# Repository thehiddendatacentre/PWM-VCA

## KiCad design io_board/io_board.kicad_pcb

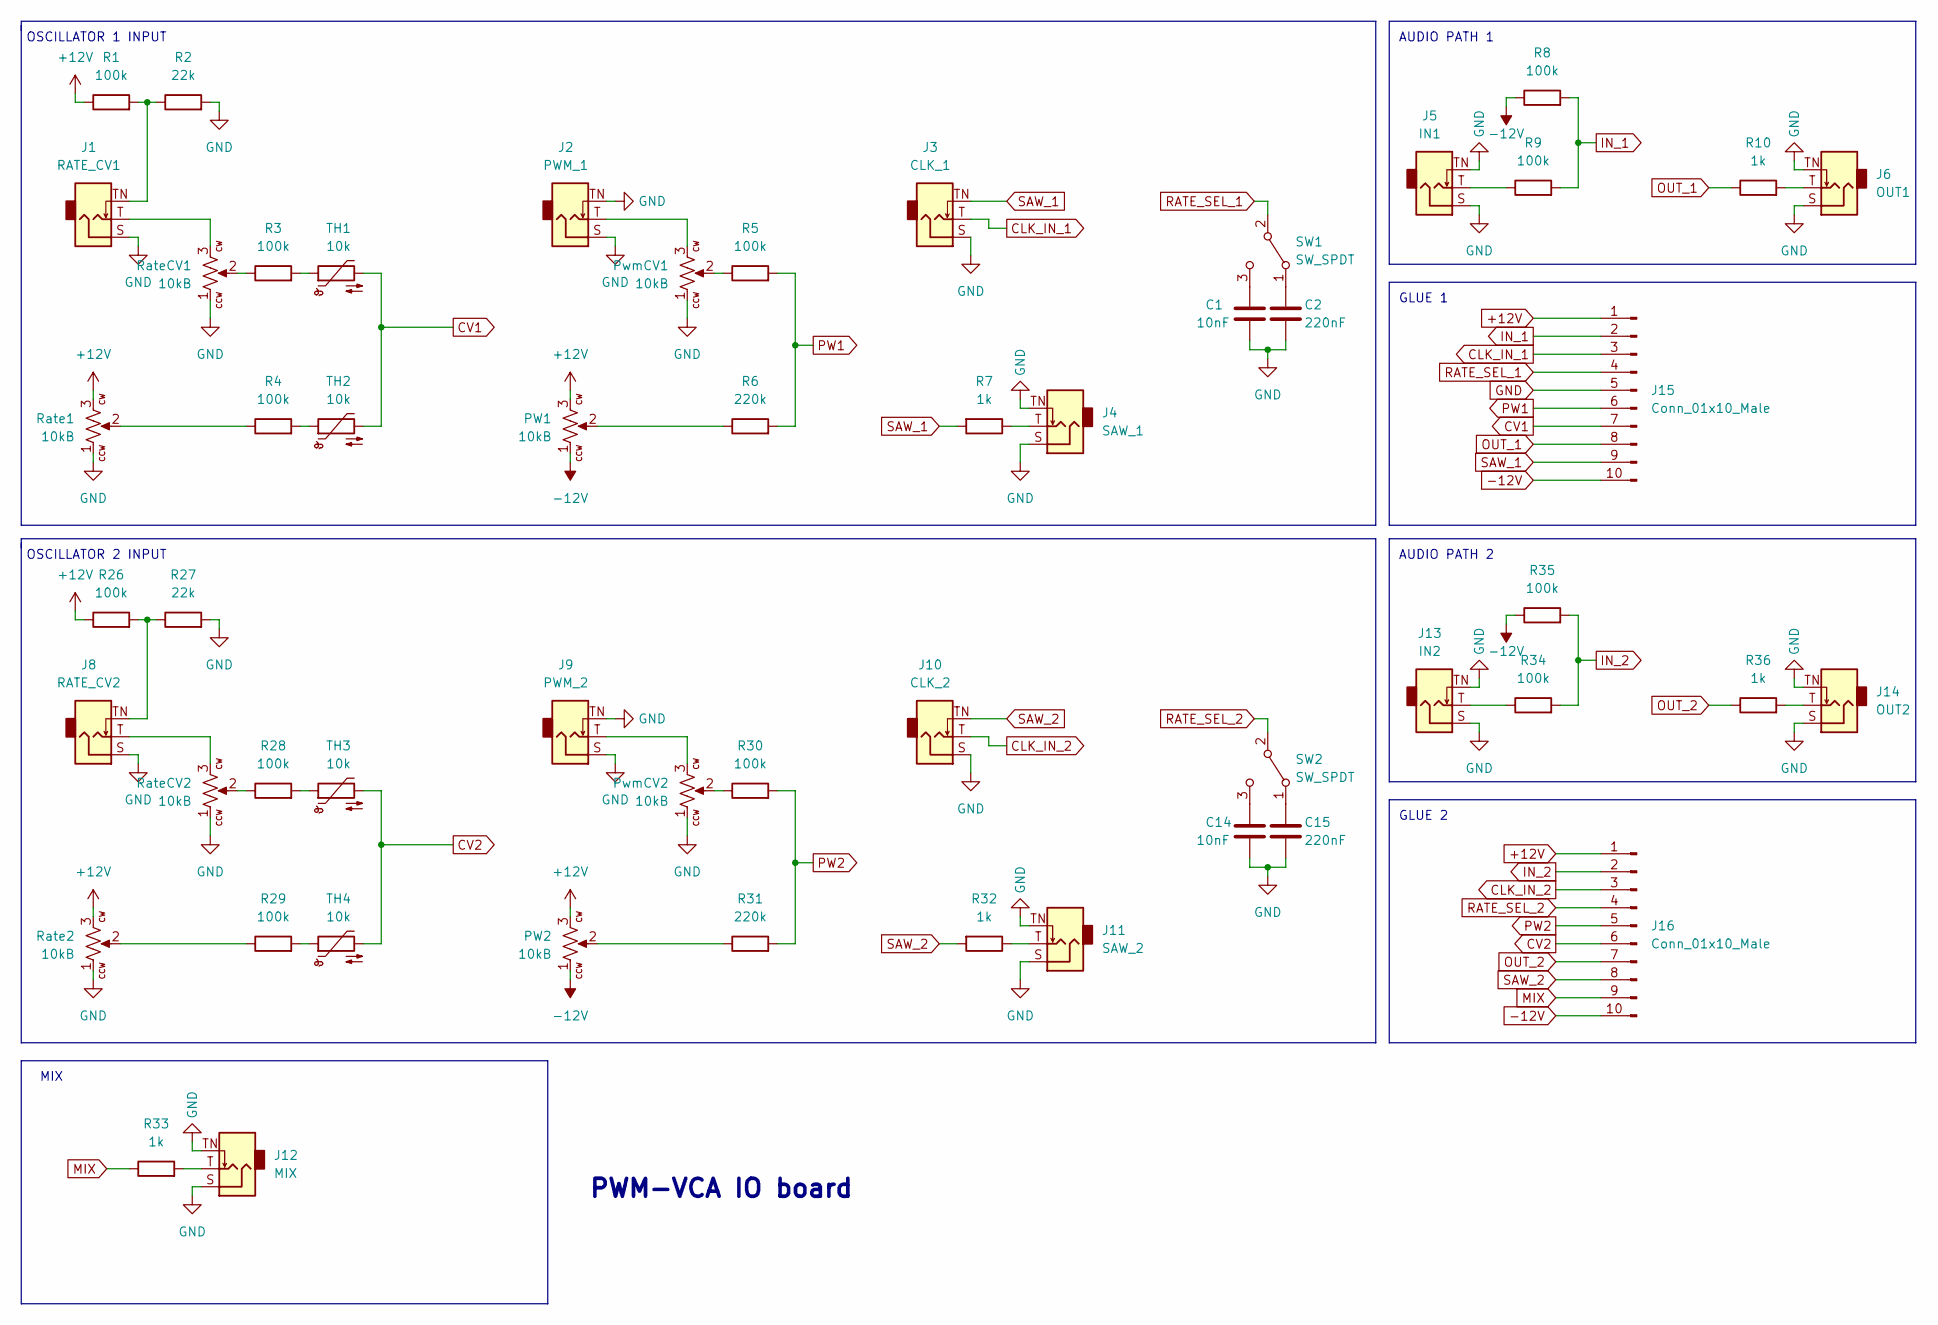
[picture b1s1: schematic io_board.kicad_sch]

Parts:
C1, C14: 10nF; C_Disc_D5.0mm_W2.5mm_P2.50mm
C2, C15: 220nF; C_Disc_D5.0mm_W2.5mm_P2.50mm
J1: RATE_CV1; AudioJack_WQP518MA; MPN WQP-WQP518MA
J2: PWM_1; AudioJack_WQP518MA; MPN WQP-WQP518MA
J3: CLK_1; AudioJack_WQP518MA; MPN WQP-WQP518MA
J4: SAW_1; AudioJack_WQP518MA; MPN WQP-WQP518MA
J5: IN1; AudioJack_WQP518MA; MPN WQP-WQP518MA
J6: OUT1; AudioJack_WQP518MA; MPN WQP-WQP518MA
J8: RATE_CV2; AudioJack_WQP518MA; MPN WQP-WQP518MA
J9: PWM_2; AudioJack_WQP518MA; MPN WQP-WQP518MA
J10: CLK_2; AudioJack_WQP518MA; MPN WQP-WQP518MA
J11: SAW_2; AudioJack_WQP518MA; MPN WQP-WQP518MA
J12: MIX; AudioJack_WQP518MA; MPN WQP-WQP518MA
J13: IN2; AudioJack_WQP518MA; MPN WQP-WQP518MA
J14: OUT2; AudioJack_WQP518MA; MPN WQP-WQP518MA
J15, J16: Conn_01x10_Male
PW1, PW2: 10kB; Potentiometer_Alpha_R0904N; MPN R0904N-???? L-25KQ/LWS
PwmCV1, PwmCV2: 10kB; Potentiometer_Alpha_R0904N; MPN R0904N-???? L-25KQ/LWS
R1, R3, R4, R5, R8, R9, R26, R28, R29, R30, R34, R35: 100k; R_Axial_DIN0204_L3.6mm_D1.6mm_P7.62mm_Horizontal
R2, R27: 22k; R_Axial_DIN0204_L3.6mm_D1.6mm_P7.62mm_Horizontal
R6, R31: 220k; R_Axial_DIN0204_L3.6mm_D1.6mm_P7.62mm_Horizontal
R7, R10, R32, R33, R36: 1k; R_Axial_DIN0204_L3.6mm_D1.6mm_P7.62mm_Horizontal
Rate1, Rate2: 10kB; Potentiometer_Alpha_R0904N; MPN R0904N-???? L-25KQ/LWS
RateCV1, RateCV2: 10kB; Potentiometer_Alpha_R0904N; MPN R0904N-???? L-25KQ/LWS
SW1, SW2: SW_SPDT; Miniature_Switch_SPDT_2.54MM
TH1, TH2, TH3, TH4: 10k; R_Axial_DIN0204_L3.6mm_D1.6mm_P2.54mm_Vertical

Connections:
+12V: J15.1, J16.1, PW1.3, PW2.3, R1.1, R26.1, Rate1.3, Rate2.3
-12V: J15.10, J16.10, PW1.1, PW2.1, R8.1, R35.1
CLK_IN_1: J3.T (Tip), J15.3
CLK_IN_2: J10.T (Tip), J16.3
CV1: J15.7, TH1.2, TH2.2
CV2: J16.6, TH3.2, TH4.2
GND: C1.2, C2.2, C14.2, C15.2, J1.S (Sleeve), J2.S (Sleeve), J2.TN (Tip_normalize), J3.S (Sleeve), J4.S (Sleeve), J4.TN (Tip_normalize), J5.S (Sleeve), J5.TN (Tip_normalize), J6.S (Sleeve), J6.TN (Tip_normalize), J8.S (Sleeve), J9.S (Sleeve), J9.TN (Tip_normalize), J10.S (Sleeve), J11.S (Sleeve), J11.TN (Tip_normalize), J12.S (Sleeve), J12.TN (Tip_normalize), J13.S (Sleeve), J13.TN (Tip_normalize), J14.S (Sleeve), J14.TN (Tip_normalize), J15.5, PwmCV1.1, PwmCV2.1, R2.2, R27.2, Rate1.1, Rate2.1, RateCV1.1, RateCV2.1
IN_1: J15.2, R8.2, R9.2
IN_2: J16.2, R34.2, R35.2
MIX: J16.9, R33.1
unnamed: C1.1, SW1.3 (C)
unnamed: C2.1, SW1.1 (A)
unnamed: C14.1, SW2.3 (C)
unnamed: C15.1, SW2.1 (A)
unnamed: J1.T (Tip), RateCV1.3
unnamed: J1.TN (Tip_normalize), R1.2, R2.1
unnamed: J2.T (Tip), PwmCV1.3
unnamed: J4.T (Tip), R7.1
unnamed: J5.T (Tip), R9.1
unnamed: J6.T (Tip), R10.2
unnamed: J8.T (Tip), RateCV2.3
unnamed: J8.TN (Tip_normalize), R26.2, R27.1
unnamed: J9.T (Tip), PwmCV2.3
unnamed: J11.T (Tip), R32.1
unnamed: J12.T (Tip), R33.2
unnamed: J13.T (Tip), R34.1
unnamed: J14.T (Tip), R36.2
unnamed: PW1.2, R6.1
unnamed: PW2.2, R31.1
unnamed: PwmCV1.2, R5.1
unnamed: PwmCV2.2, R30.1
unnamed: R3.1, RateCV1.2
unnamed: R3.2, TH1.1
unnamed: R4.1, Rate1.2
unnamed: R4.2, TH2.1
unnamed: R28.1, RateCV2.2
unnamed: R28.2, TH3.1
unnamed: R29.1, Rate2.2
unnamed: R29.2, TH4.1
OUT_1: J15.8, R10.1
OUT_2: J16.7, R36.1
PW1: J15.6, R5.2, R6.2
PW2: J16.5, R30.2, R31.2
RATE_SEL_1: J15.4, SW1.2 (B)
RATE_SEL_2: J16.4, SW2.2 (B)
SAW_1: J3.TN (Tip_normalize), J15.9, R7.2
SAW_2: J10.TN (Tip_normalize), J16.8, R32.2

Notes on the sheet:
AUDIO PATH 2
GLUE 1
MIX
OSCILLATOR 2 INPUT
OSCILLATOR 1 INPUT
GLUE 2
PWM-VCA IO board
AUDIO PATH 1

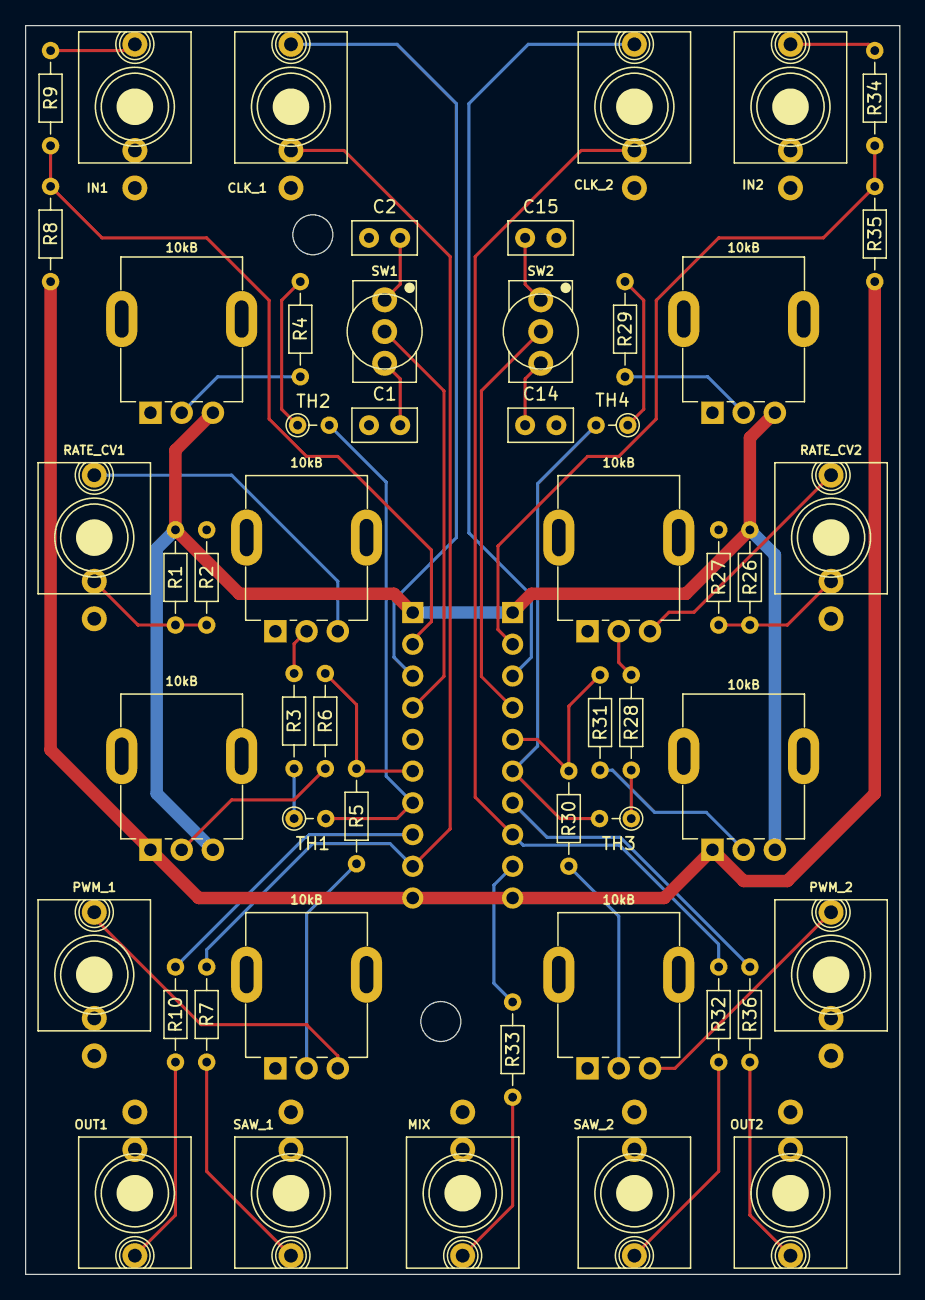
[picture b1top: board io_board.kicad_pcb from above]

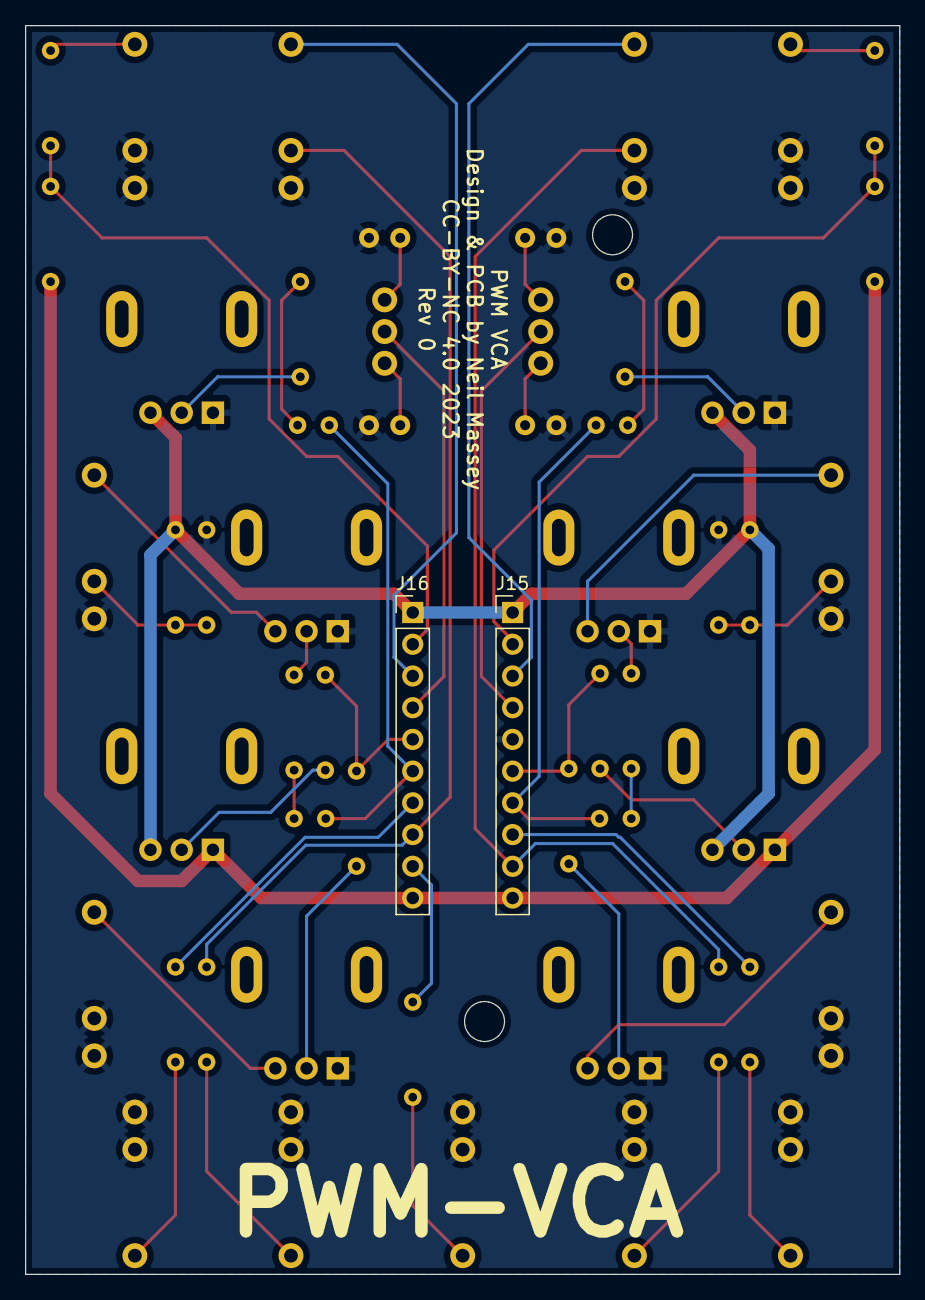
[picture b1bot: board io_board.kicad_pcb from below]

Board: 2 copper layers, 70.0 x 100.0 mm, 54 parts (2 on the bottom side), 47 nets.

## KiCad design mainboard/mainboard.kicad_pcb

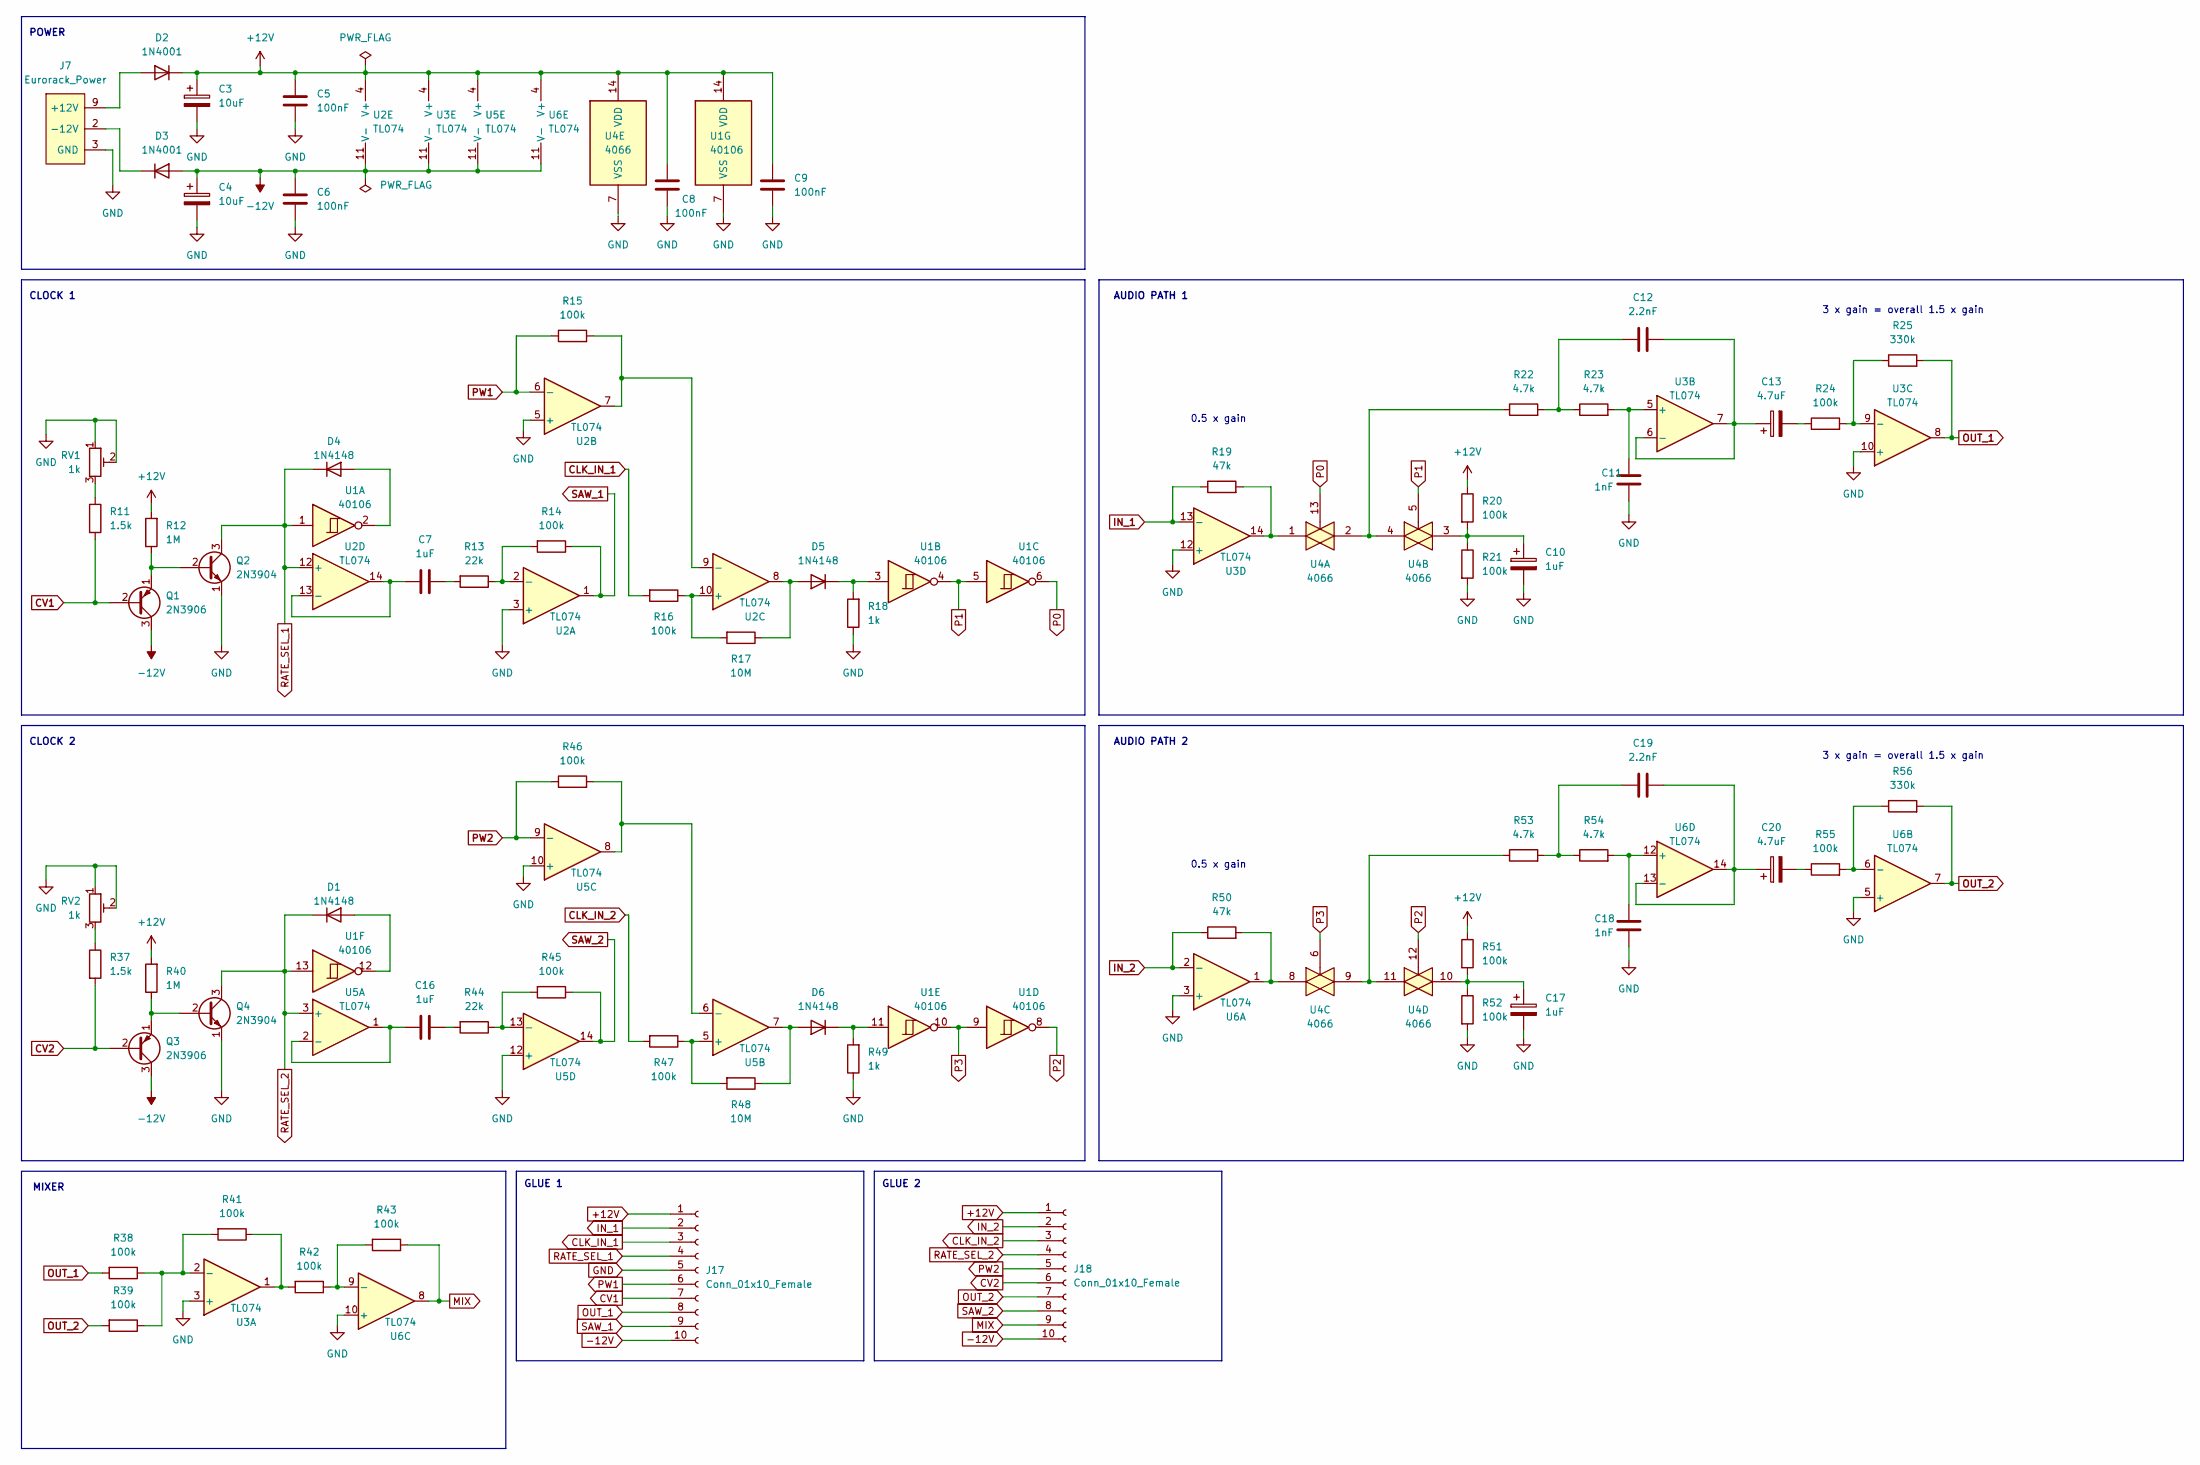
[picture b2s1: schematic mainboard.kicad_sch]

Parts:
C3, C4: 10uF; CP_Radial_D5.0mm_P2.00mm
C5, C6: 100nF; C_Disc_D5.0mm_W2.5mm_P2.50mm
C7, C16: 1uF; C_Disc_D5.0mm_W2.5mm_P2.50mm
C8, C9: 100nF; C_Disc_D7.0mm_W2.5mm_P5.00mm
C10, C17: 1uF; CP_Radial_D5.0mm_P2.00mm
C11, C18: 1nF; C_Disc_D7.5mm_W2.5mm_P5.00mm
C12, C19: 2.2nF; C_Disc_D7.5mm_W2.5mm_P5.00mm
C13, C20: 4.7uF; CP_Radial_D5.0mm_P2.00mm
D1, D4, D5, D6: 1N4148; D_DO-35_SOD27_P7.62mm_Horizontal
D2, D3: 1N4001; D_DO-41_SOD81_P10.16mm_Horizontal
J7: Eurorack_Power; Eurorack_Power_2x5_Shrouded; MPN 302-S101
J17, J18: Conn_01x10_Female; PinSocket_1x10_P2.54mm_Vertical
Q1, Q3: 2N3906; TO-92_Inline
Q2, Q4: 2N3904; TO-92_Inline
R11, R37: 1.5k; R_Axial_DIN0204_L3.6mm_D1.6mm_P7.62mm_Horizontal
R12, R40: 1M; R_Axial_DIN0204_L3.6mm_D1.6mm_P7.62mm_Horizontal
R13, R44: 22k; R_Axial_DIN0204_L3.6mm_D1.6mm_P7.62mm_Horizontal
R14, R15, R16, R20, R21, R24, R38, R39, R41, R42, R43, R45, R46, R47, R51, R52, R55: 100k; R_Axial_DIN0204_L3.6mm_D1.6mm_P7.62mm_Horizontal
R17, R48: 10M; R_Axial_DIN0204_L3.6mm_D1.6mm_P7.62mm_Horizontal
R18, R49: 1k; R_Axial_DIN0204_L3.6mm_D1.6mm_P7.62mm_Horizontal
R19, R50: 47k; R_Axial_DIN0204_L3.6mm_D1.6mm_P7.62mm_Horizontal
R22, R23, R53, R54: 4.7k; R_Axial_DIN0204_L3.6mm_D1.6mm_P7.62mm_Horizontal
R25, R56: 330k; R_Axial_DIN0204_L3.6mm_D1.6mm_P7.62mm_Horizontal
RV1, RV2: 1k; Potentiometer_Bourns_3296W_Vertical
U1: 40106; DIP-14_W7.62mm_LongPads
U2, U3, U5, U6: TL074; DIP-14_W7.62mm_LongPads
U4: 4066; DIP-14_W7.62mm_LongPads

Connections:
+12V: C3.1, C5.1, C8.1, C9.1, D2.1 (K), J17.1, J18.1, R12.2, R20.1, R40.2, R51.1, U1.14 (VDD), U2.4 (V+), U3.4 (V+), U4.14 (VDD), U5.4 (V+), U6.4 (V+)
-12V: C4.1, C6.1, D3.2 (A), J17.10, J18.10, Q1.3 (C), Q3.3 (C), U2.11 (V-), U3.11 (V-), U5.11 (V-), U6.11 (V-)
CLK_IN_1: J17.3, R16.2
CLK_IN_2: J18.3, R47.2
CV1: J17.7, Q1.2 (B), R11.2
CV2: J18.6, Q3.2 (B), R37.2
GND: C3.2, C4.2, C5.2, C6.2, C8.2, C9.2, C10.2, C11.2, C17.2, C18.2, J7.3 (GND), J7.4 (GND), J7.5 (GND), J7.6 (GND), J7.7 (GND), J7.8 (GND), J17.5, Q2.1 (E), Q4.1 (E), R18.1, R21.2, R49.1, R52.2, RV1.1, RV1.2, RV2.1, RV2.2, U1.7 (VSS), U2.3 (+), U2.5 (+), U3.3 (+), U3.10 (+), U3.12 (+), U4.7 (VSS), U5.10 (+), U5.12 (+), U6.3 (+), U6.5 (+), U6.10 (+)
IN_1: J17.2, R19.1, U3.13 (-)
IN_2: J18.2, R50.1, U6.2 (-)
MIX: J18.9, R43.1, U6.8
unnamed: C7.1, U2.13 (-), U2.14
unnamed: C7.2, R13.2
unnamed: C10.1, R20.2, R21.1, U4.3
unnamed: C11.1, R23.2, U3.5 (+)
unnamed: C12.1, R22.2, R23.1
unnamed: C12.2, C13.1, U3.6 (-), U3.7
unnamed: C13.2, R24.1
unnamed: C16.1, U5.1, U5.2 (-)
unnamed: C16.2, R44.2
unnamed: C17.1, R51.2, R52.1, U4.10
unnamed: C18.1, R54.2, U6.12 (+)
unnamed: C19.1, R53.2, R54.1
unnamed: C19.2, C20.1, U6.13 (-), U6.14
unnamed: C20.2, R55.1
unnamed: D1.2 (A), U1.12
unnamed: D2.2 (A), J7.9 (+12V), J7.10 (+12V)
unnamed: D3.1 (K), J7.1 (-12V), J7.2 (-12V)
unnamed: D4.2 (A), U1.2
unnamed: D5.1 (K), R18.2, U1.3
unnamed: D5.2 (A), R17.1, U2.8
unnamed: D6.1 (K), R49.2, U1.11
unnamed: D6.2 (A), R48.1, U5.7
unnamed: Q1.1 (E), Q2.2 (B), R12.1
unnamed: Q3.1 (E), Q4.2 (B), R40.1
unnamed: R11.1, RV1.3
unnamed: R13.1, R14.2, U2.2 (-)
unnamed: R15.2, U2.7, U2.9 (-)
unnamed: R16.1, R17.2, U2.10 (+)
unnamed: R19.2, U3.14, U4.1
unnamed: R22.1, U4.2, U4.4
unnamed: R24.2, R25.1, U3.9 (-)
unnamed: R37.1, RV2.3
unnamed: R38.1, R39.1, R41.2, U3.2 (-)
unnamed: R41.1, R42.2, U3.1
unnamed: R42.1, R43.2, U6.9 (-)
unnamed: R44.1, R45.2, U5.13 (-)
unnamed: R46.2, U5.6 (-), U5.8
unnamed: R47.1, R48.2, U5.5 (+)
unnamed: R50.2, U4.8, U6.1
unnamed: R53.1, U4.9, U4.11
unnamed: R55.2, R56.1, U6.6 (-)
OUT_1: J17.8, R25.2, R38.2, U3.8
OUT_2: J18.7, R39.2, R56.2, U6.7
P0: U1.6, U4.13
P1: U1.4, U1.5, U4.5
P2: U1.8, U4.12
P3: U1.9, U1.10, U4.6
PW1: J17.6, R15.1, U2.6 (-)
PW2: J18.5, R46.1, U5.9 (-)
RATE_SEL_1: D4.1 (K), J17.4, Q2.3 (C), U1.1, U2.12 (+)
RATE_SEL_2: D1.1 (K), J18.4, Q4.3 (C), U1.13, U5.3 (+)
SAW_1: J17.9, R14.1, U2.1
SAW_2: J18.8, R45.1, U5.14

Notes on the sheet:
CLOCK 1
POWER
GLUE 1
AUDIO PATH 2
CLOCK 2
3 x gain = overall 1.5 x gain
GLUE 2
0.5 x gain
AUDIO PATH 1
MIXER

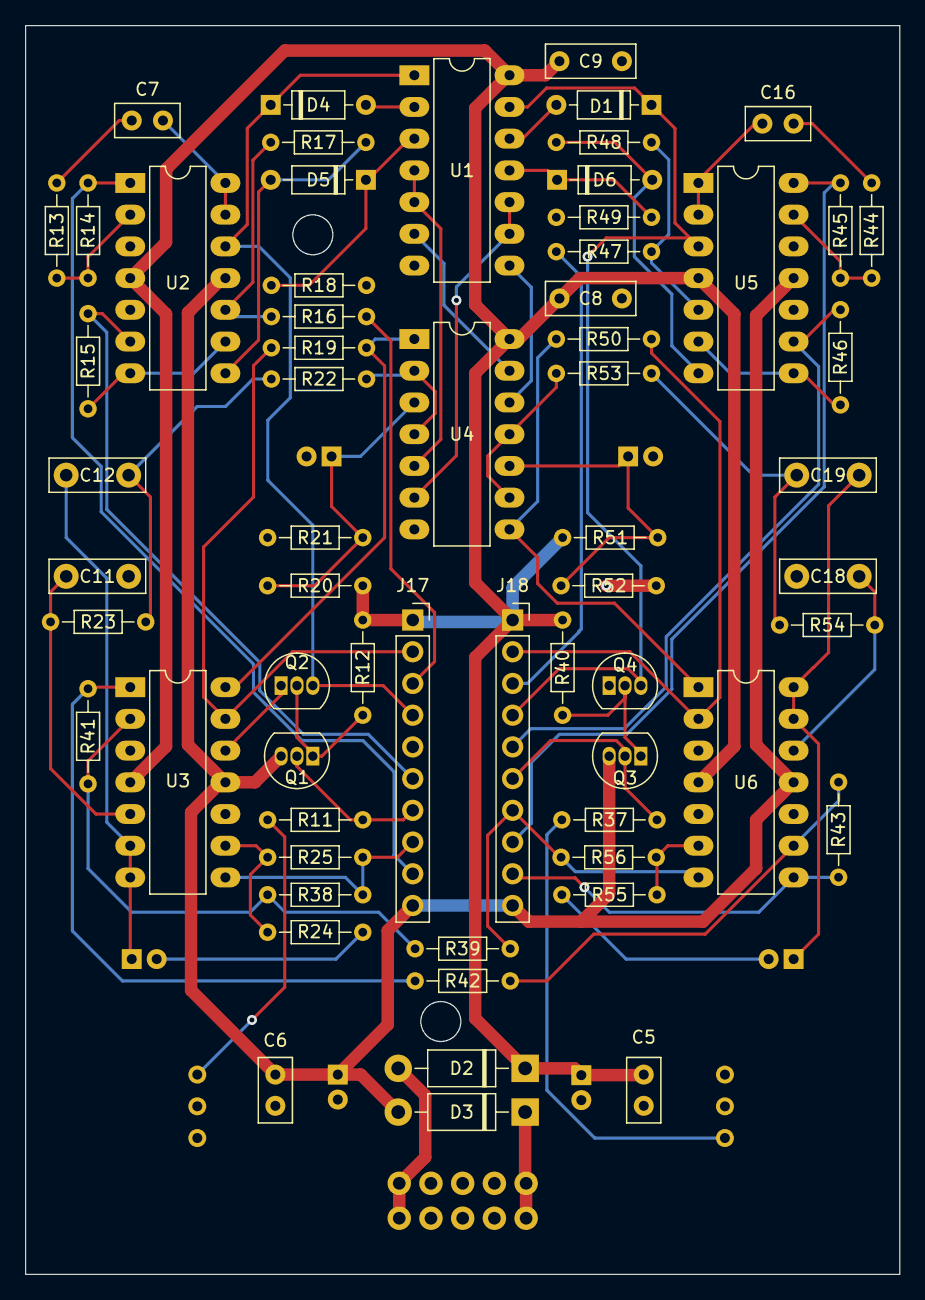
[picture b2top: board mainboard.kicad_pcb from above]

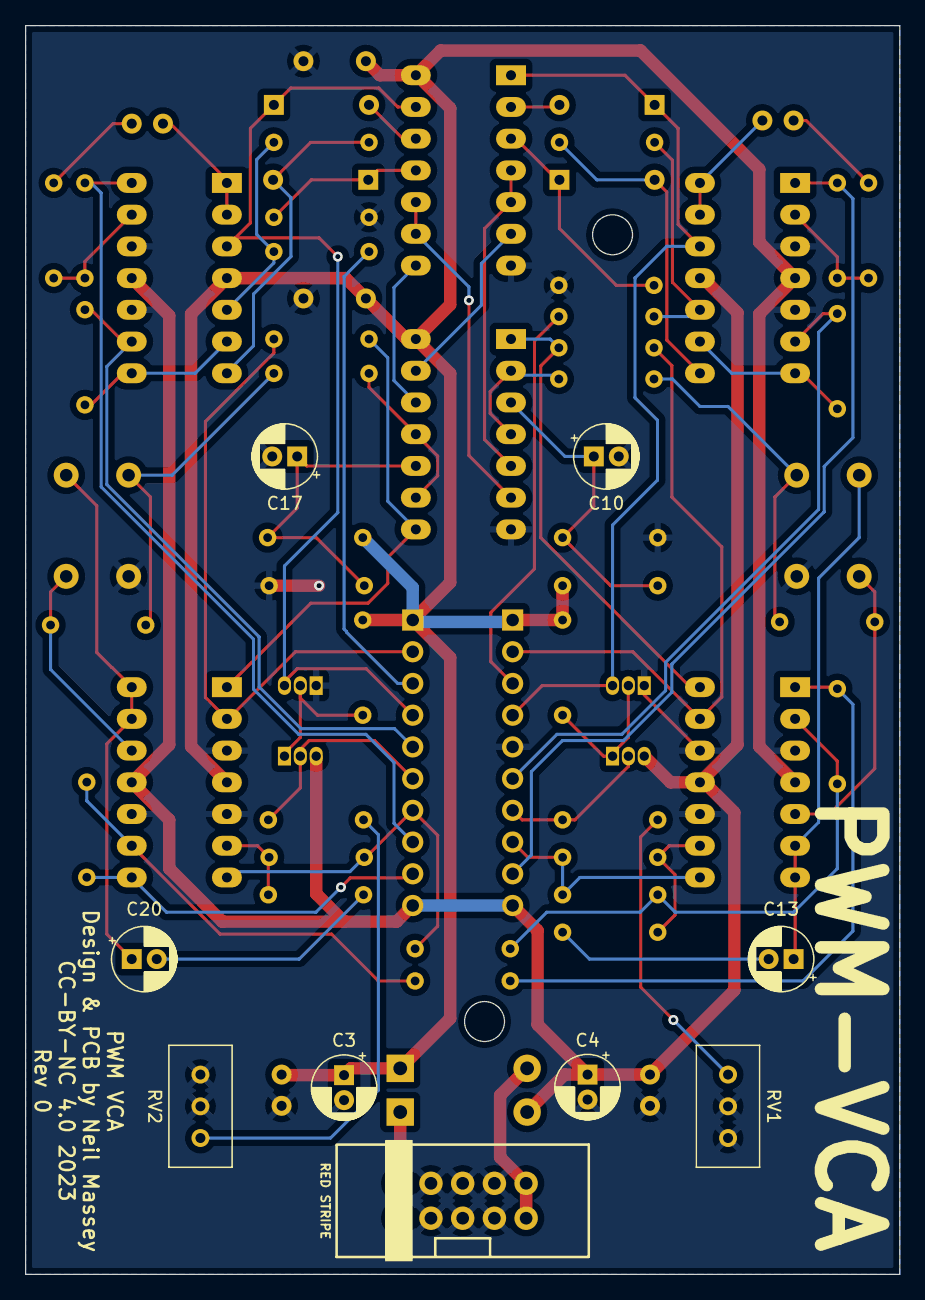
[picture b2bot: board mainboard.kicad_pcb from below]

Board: 2 copper layers, 70.0 x 100.0 mm, 72 parts (9 on the bottom side), 63 nets.

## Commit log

2023-02-25 Added LICENSE
2023-02-25 Changed mounting holes
2023-03-03 Changed inputs to circles on panels

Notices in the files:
io_board/io_board.kicad_pcb:
CC-BY-NC 4.0 2023
